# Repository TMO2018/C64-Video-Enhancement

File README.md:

# C64 Video Enhancement

The original project can be found here:
https://github.com/c0pperdragon

I've made some changes to the VIC II-Adapter pcb and the rfreplacement pcb.

# VIC II-Adapter (A-VideoBoard c64board)
Rev 3.1 is based on c0pperdragons Rev 3
- Fits better with a 407-board
- Layout for hand soldering (SMD 0805)

# rfreplacment
Rev 6.1 is based on c0pperdragons Rev 6
- Layout for hand soldering (SMD 0805)
- Video connector ist placed in the middle of the hole in the C64-housing

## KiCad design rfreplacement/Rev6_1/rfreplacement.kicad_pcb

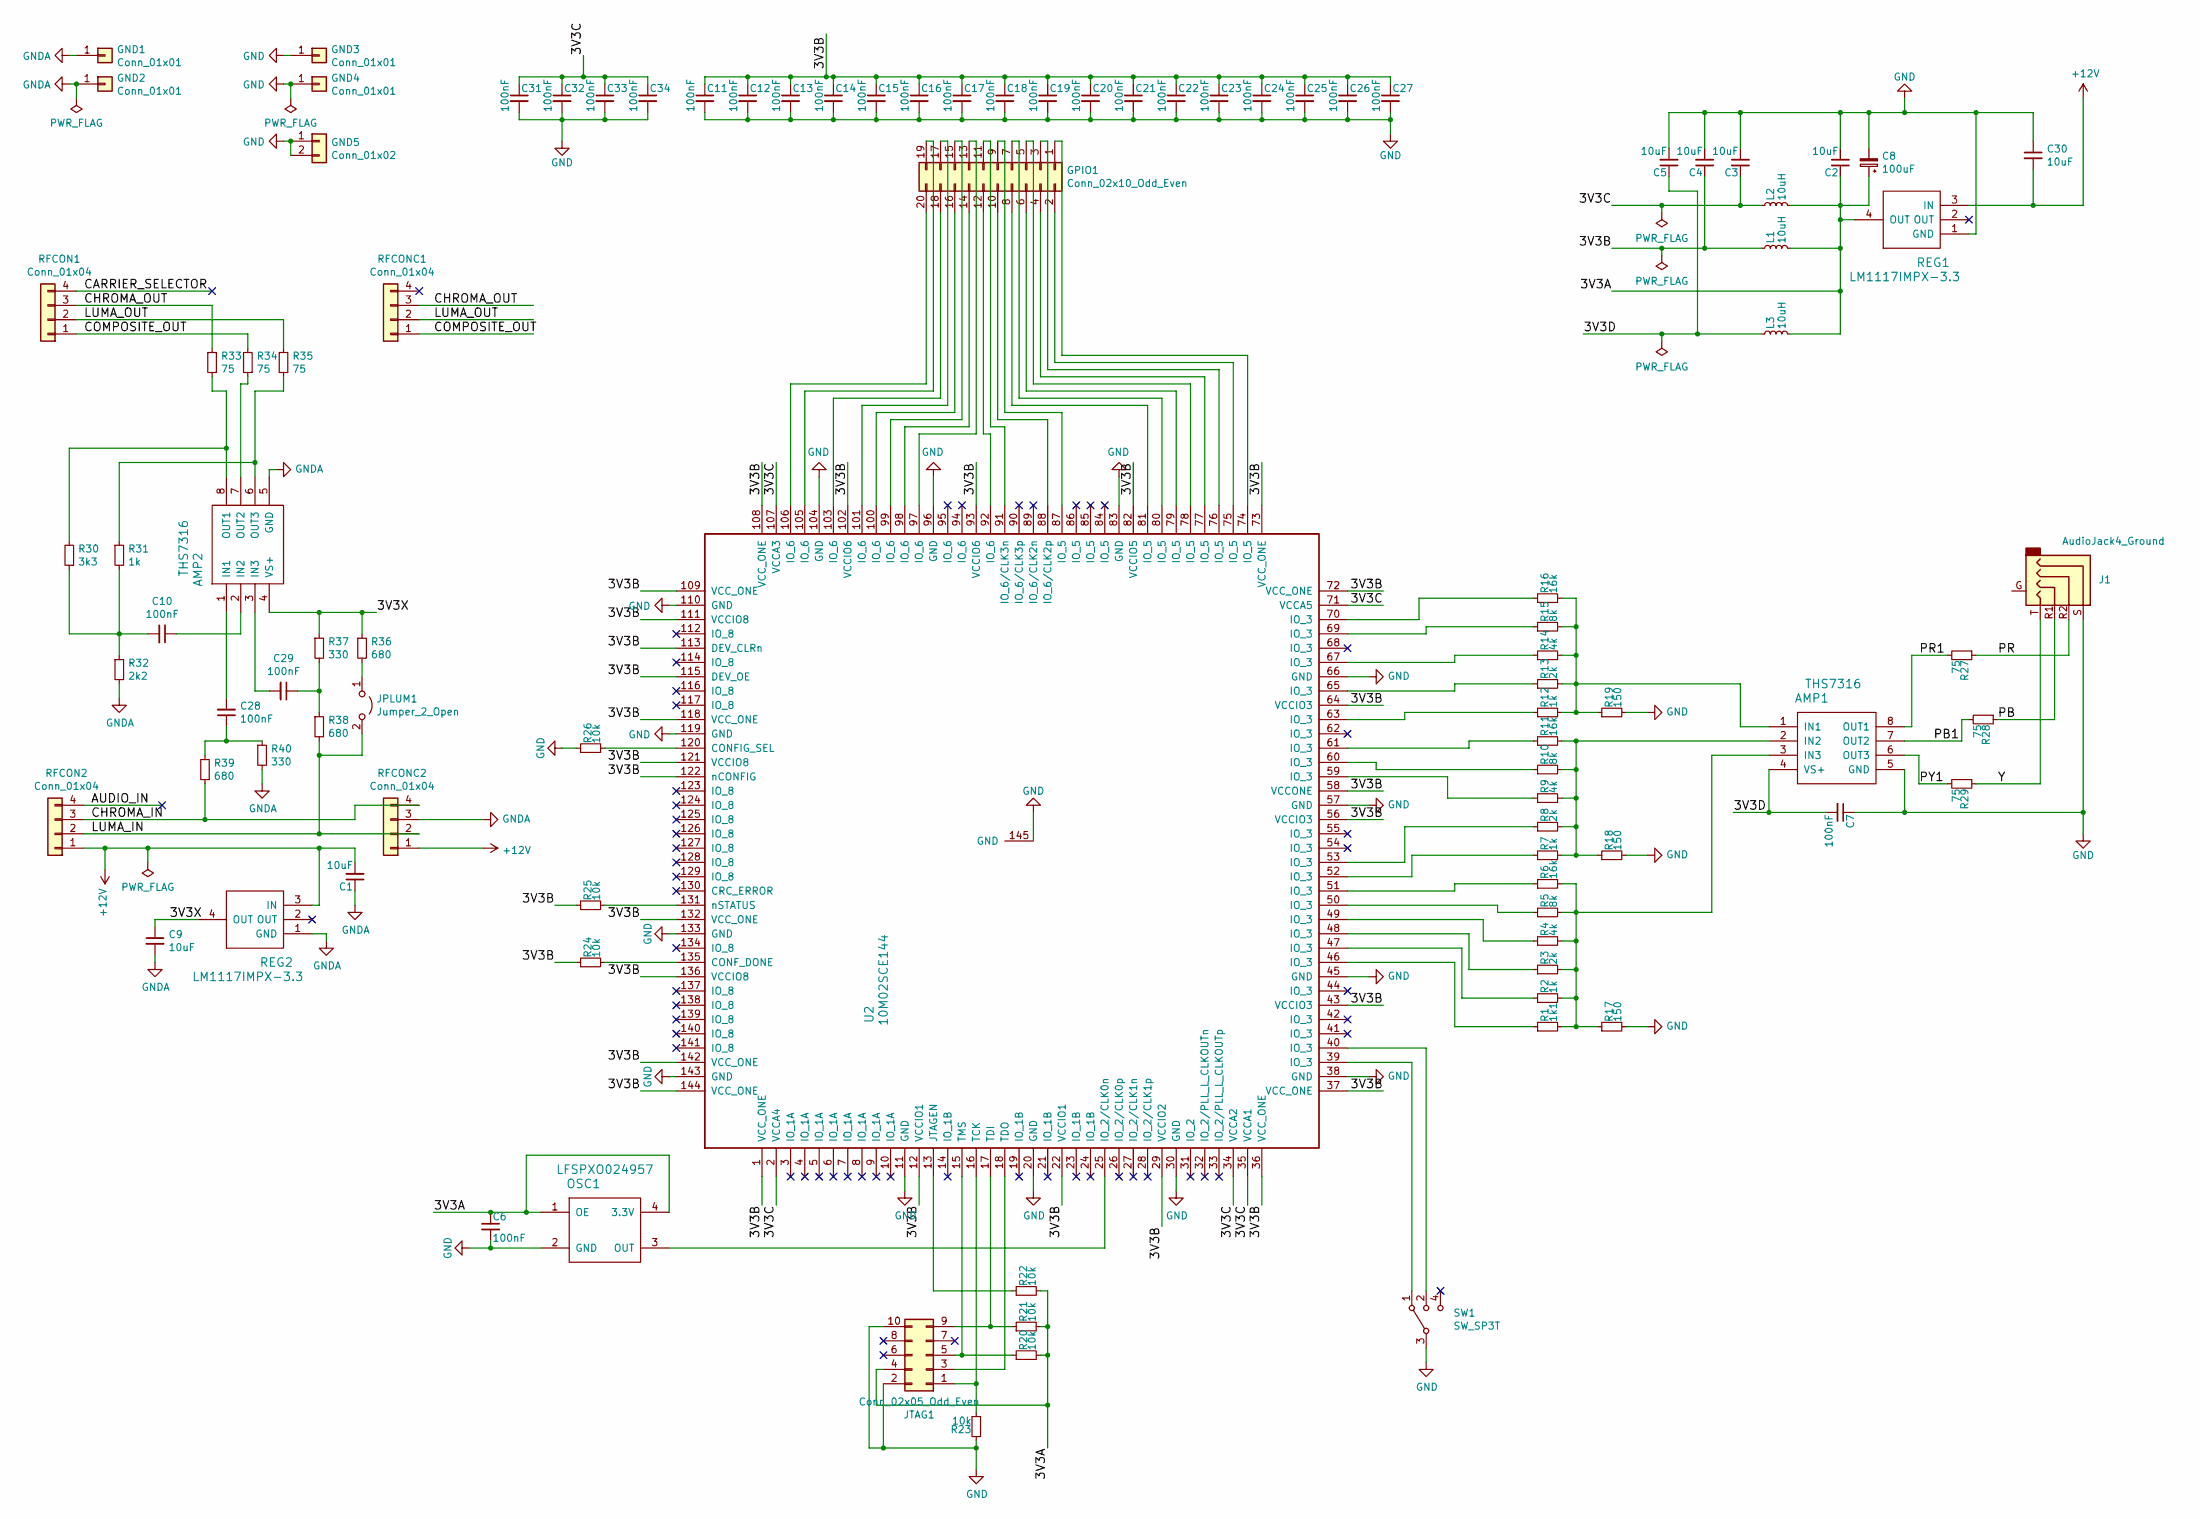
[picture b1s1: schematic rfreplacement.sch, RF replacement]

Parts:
AMP1, AMP2: THS7316; SSOP-8_3.9x5.05mm_P1.27mm
C1, C2, C3, C4, C5, C9, C30: 10uF; C_0805_HandSoldering
C6, C7, C10, C11, C12, C13, C14, C15, C16, C17, C18, C19, C20, C21, C22, C23, C24, C25, C26, C27, C28, C29, C31, C32, C33, C34: 100nF; C_0805_HandSoldering
C8: 100uF; CP_Radial_D8.0mm_P3.50mm
GND1, GND2, GND3, GND4: Conn_01x01; Pin_Header_Straight_1x01_Pitch2.54mm
GND5: Conn_01x02; Pin_Header_Straight_1x02_Pitch2.54mm
GPIO1: Conn_02x10_Odd_Even; Pin_Header_Straight_2x10_Pitch2.54mm
J1: AudioJack4_Ground; Conrad 4pin audio jack
JPLUM1: Jumper_2_Open; SolderJumper-2_P1.3mm_Open_RoundedPad1.0x1.5mm
JTAG1: Conn_02x05_Odd_Even; Pin_Header_Straight_2x05_Pitch2.54mm
L1, L2, L3: 10uH; L_0805_HandSoldering
OSC1: LFSPXO024957; Oscillator_SMD_EuroQuartz_XO53-4pin_5.0x3.2mm_HandSoldering
R1: 1k1; R_0805_HandSoldering
R2, R7, R12, R31: 1k; R_0805_HandSoldering
R3, R8, R13: 2k; R_0805_HandSoldering
R4, R9, R14: 4k; R_0805_HandSoldering
R5, R10, R15: 8k; R_0805_HandSoldering
R6, R11, R16: 16k; R_0805_HandSoldering
R17, R18, R19: 150; R_0805_HandSoldering
R20, R21, R22, R23, R24, R25, R26: 10k; R_0805_HandSoldering
R27, R28, R29, R33, R34, R35: 75; R_0805_HandSoldering
R30: 3k3; R_0805_HandSoldering
R32: 2k2; R_0805_HandSoldering
R36, R38, R39: 680; R_0805_HandSoldering
R37, R40: 330; R_0805_HandSoldering
REG1, REG2: LM1117IMPX-3.3; SOT-223
RFCON1, RFCON2: Conn_01x04; Pin_Header_Straight_1x04_Pitch2.54mm
RFCONC1, RFCONC2: Conn_01x04; Pin_Header_Straight_1x04_Pitch2.54mm
SW1: SW_SP3T; slider
U2: 10M02SCE144; EQFP-144-1EP_20x20mm_P0.5mm_EP8.93x8.7mm_ThermalVias

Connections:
+12V: C1.2, C30.2, REG1.3 (IN), REG2.3 (IN), RFCON2.1, RFCONC2.1
/3V3A: C2.1, C6.1, C8.1, JTAG1.4, L1.2, L2.2, L3.2, OSC1.1 (OE), OSC1.4 (3.3V), R20.2, R21.2, R22.2, REG1.4 (OUT)
/3V3B: C4.1, C11.1, C12.1, C13.1, C14.1, C15.1, C16.1, C17.1, C18.1, C19.1, C20.1, C21.1, C22.1, C23.1, C24.1, C25.1, C26.1, C27.1, L1.1, R24.1, R25.1, U2.1 (VCC_ONE), U2.12 (VCCIO1), U2.22 (VCCIO1), U2.29 (VCCIO2), U2.36 (VCC_ONE), U2.37 (VCC_ONE), U2.43 (VCCIO3), U2.56 (VCCIO3), U2.58 (VCCONE), U2.64 (VCCIO3), U2.72 (VCC_ONE), U2.73 (VCC_ONE), U2.82 (VCCIO5), U2.93 (VCCIO6), U2.102 (VCCIO6), U2.108 (VCC_ONE), U2.109 (VCC_ONE), U2.111 (VCCIO8), U2.113 (DEV_CLRn), U2.115 (DEV_OE), U2.118 (VCC_ONE), U2.121 (VCCIO8), U2.122 (nCONFIG), U2.132 (VCC_ONE), U2.136 (VCCIO8), U2.142 (VCC_ONE), U2.144 (VCC_ONE)
/3V3C: C3.1, C31.1, C32.1, C33.1, C34.1, L2.1, U2.2 (VCCA4), U2.34 (VCCA2), U2.35 (VCCA1), U2.71 (VCCA5), U2.107 (VCCA3)
/3V3D: AMP1.4 (VS+), C5.1, C7.2, L3.1
/3V3X: AMP2.4 (VS+), C9.1, R36.1, R37.1, REG2.4 (OUT)
/CHROMA_IN: R39.1, RFCON2.3, RFCONC2.4
/CHROMA_OUT: R33.1, RFCON1.3, RFCONC1.3
/COMPOSITE_OUT: R34.2, RFCON1.1, RFCONC1.1
/LUMA_IN: JPLUM1.2 (B), R38.2, RFCON2.2, RFCONC2.2
/LUMA_OUT: R35.1, RFCON1.2, RFCONC1.2
/PB: J1.R1, R28.1
/PB1: AMP1.7 (OUT2), R28.2
/PR: J1.R2, R27.1
/PR1: AMP1.8 (OUT1), R27.2
/PY1: AMP1.6 (OUT3), R29.2
/Y: J1.T, R29.1
GND: AMP1.5 (GND), C2.2, C3.2, C4.2, C5.2, C6.2, C7.1, C8.2, C11.2, C12.2, C13.2, C14.2, C15.2, C16.2, C17.2, C18.2, C19.2, C20.2, C21.2, C22.2, C23.2, C24.2, C25.2, C26.2, C27.2, C30.1, C31.2, C32.2, C33.2, C34.2, GND3.1, GND4.1, GND5.1, GND5.2, J1.S, JTAG1.2, JTAG1.10, OSC1.2 (GND), R17.2, R18.2, R19.2, R23.1, R26.1, REG1.1 (GND), SW1.3, U2.11 (GND), U2.20 (GND), U2.30 (GND), U2.38 (GND), U2.45 (GND), U2.57 (GND), U2.66 (GND), U2.83 (GND), U2.96 (GND), U2.104 (GND), U2.110 (GND), U2.119 (GND), U2.133 (GND), U2.143 (GND), U2.145 (GND)
GNDA: AMP2.5 (GND), C1.1, C9.2, GND1.1, GND2.1, R32.2, R40.2, REG2.1 (GND), RFCONC2.3
unnamed: AMP1.1 (IN1), R12.2, R13.2, R14.2, R15.2, R16.2, R19.1
unnamed: AMP1.2 (IN2), R7.2, R8.2, R9.2, R10.2, R11.2, R18.1
unnamed: AMP1.3 (IN3), R1.2, R2.2, R3.2, R4.2, R5.2, R6.2, R17.1
unnamed: AMP2.1 (IN1), C28.2
unnamed: AMP2.2 (IN2), C10.1
unnamed: AMP2.3 (IN3), C29.2
unnamed: AMP2.6 (OUT3), R31.1, R35.2
unnamed: AMP2.7 (OUT2), R34.1
unnamed: AMP2.8 (OUT1), R30.2, R33.2
unnamed: C10.2, R30.1, R31.2, R32.1
unnamed: C28.1, R39.2, R40.1
unnamed: C29.1, R37.2, R38.1
unnamed: GPIO1.1, U2.74 (IO_5)
unnamed: GPIO1.2, U2.75 (IO_5)
unnamed: GPIO1.3, U2.76 (IO_5)
unnamed: GPIO1.4, U2.77 (IO_5)
unnamed: GPIO1.5, U2.78 (IO_5)
unnamed: GPIO1.6, U2.79 (IO_5)
unnamed: GPIO1.7, U2.80 (IO_5)
unnamed: GPIO1.8, U2.81 (IO_5)
unnamed: GPIO1.9, U2.87 (IO_5)
unnamed: GPIO1.10, U2.88 (IO_6/CLK2p)
unnamed: GPIO1.11, U2.91 (IO_6/CLK3n)
unnamed: GPIO1.12, U2.92 (IO_6)
unnamed: GPIO1.13, U2.97 (IO_6)
unnamed: GPIO1.14, U2.98 (IO_6)
unnamed: GPIO1.15, U2.99 (IO_6)
unnamed: GPIO1.16, U2.100 (IO_6)
unnamed: GPIO1.17, U2.101 (IO_6)
unnamed: GPIO1.18, U2.103 (IO_6)
unnamed: GPIO1.19, U2.105 (IO_6)
unnamed: GPIO1.20, U2.106 (IO_6)
unnamed: JPLUM1.1 (A), R36.2
unnamed: JTAG1.1, R23.2, U2.16 (TCK)
unnamed: JTAG1.3, U2.18 (TDO)
unnamed: JTAG1.5, R20.1, U2.15 (TMS)
unnamed: JTAG1.9, R21.1, U2.17 (TDI)
unnamed: OSC1.3 (OUT), U2.25 (IO_2/CLK0n)
unnamed: R1.1, U2.46 (IO_3)
unnamed: R2.1, U2.47 (IO_3)
unnamed: R3.1, U2.48 (IO_3)
unnamed: R4.1, U2.49 (IO_3)
unnamed: R5.1, U2.50 (IO_3)
unnamed: R6.1, U2.51 (IO_3)
unnamed: R7.1, U2.52 (IO_3)
unnamed: R8.1, U2.53 (IO_3)
unnamed: R9.1, U2.59 (IO_3)
unnamed: R10.1, U2.60 (IO_3)
unnamed: R11.1, U2.61 (IO_3)
unnamed: R12.1, U2.63 (IO_3)
unnamed: R13.1, U2.65 (IO_3)
unnamed: R14.1, U2.67 (IO_3)
unnamed: R15.1, U2.69 (IO_3)
unnamed: R16.1, U2.70 (IO_3)
unnamed: R22.1, U2.13 (JTAGEN)
unnamed: R24.2, U2.135 (CONF_DONE)
unnamed: R25.2, U2.131 (nSTATUS)
unnamed: R26.2, U2.120 (CONFIG_SEL)
unnamed: SW1.1, U2.39 (IO_3)
unnamed: SW1.2, U2.40 (IO_3)

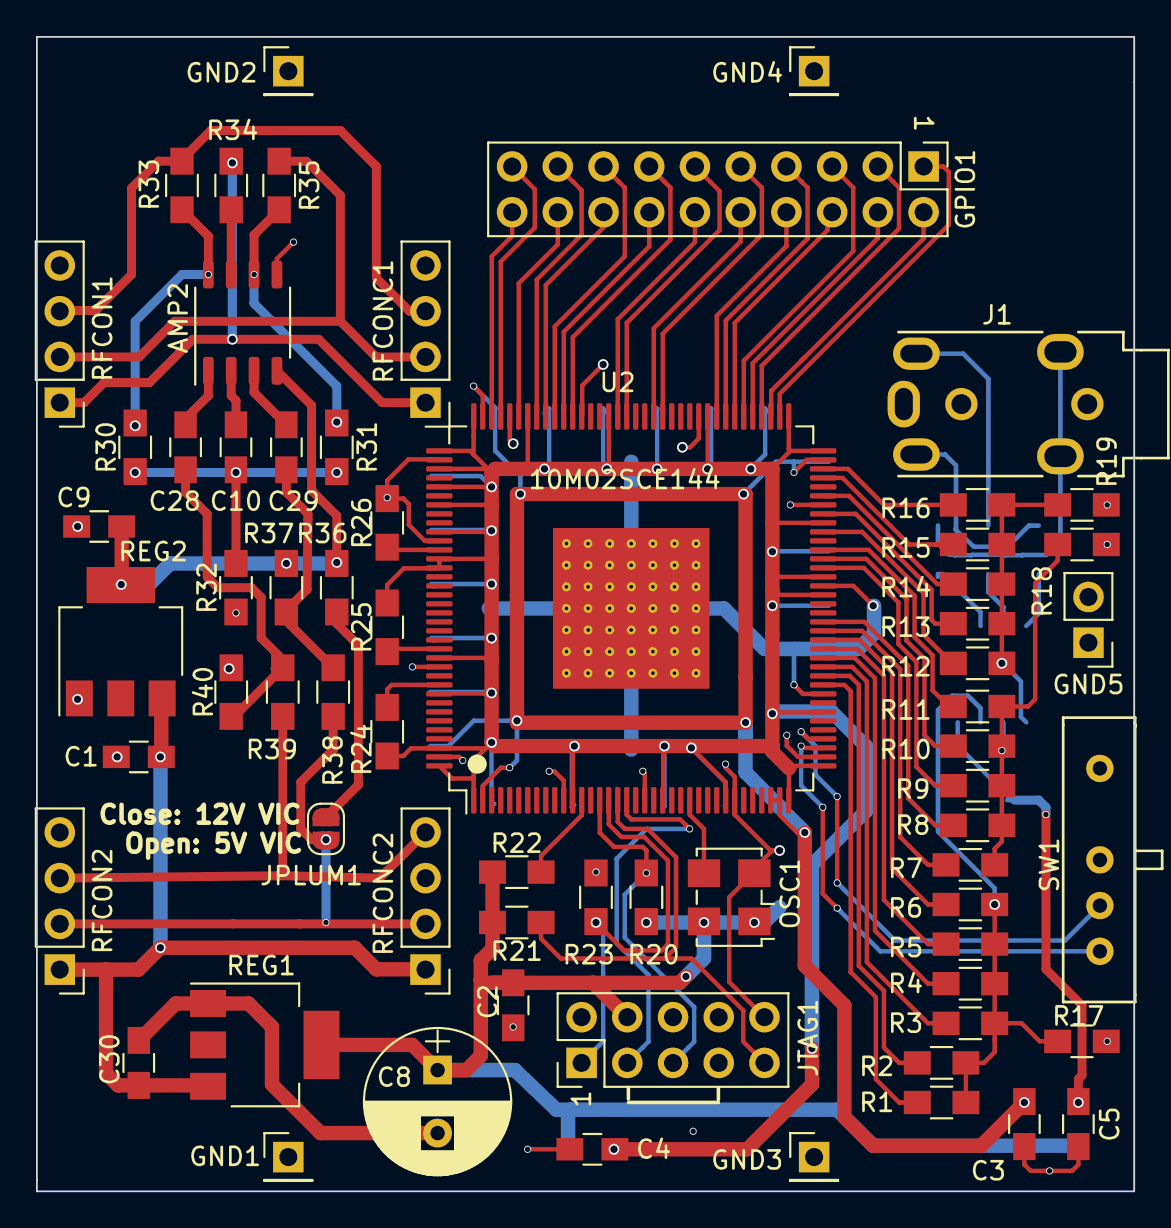
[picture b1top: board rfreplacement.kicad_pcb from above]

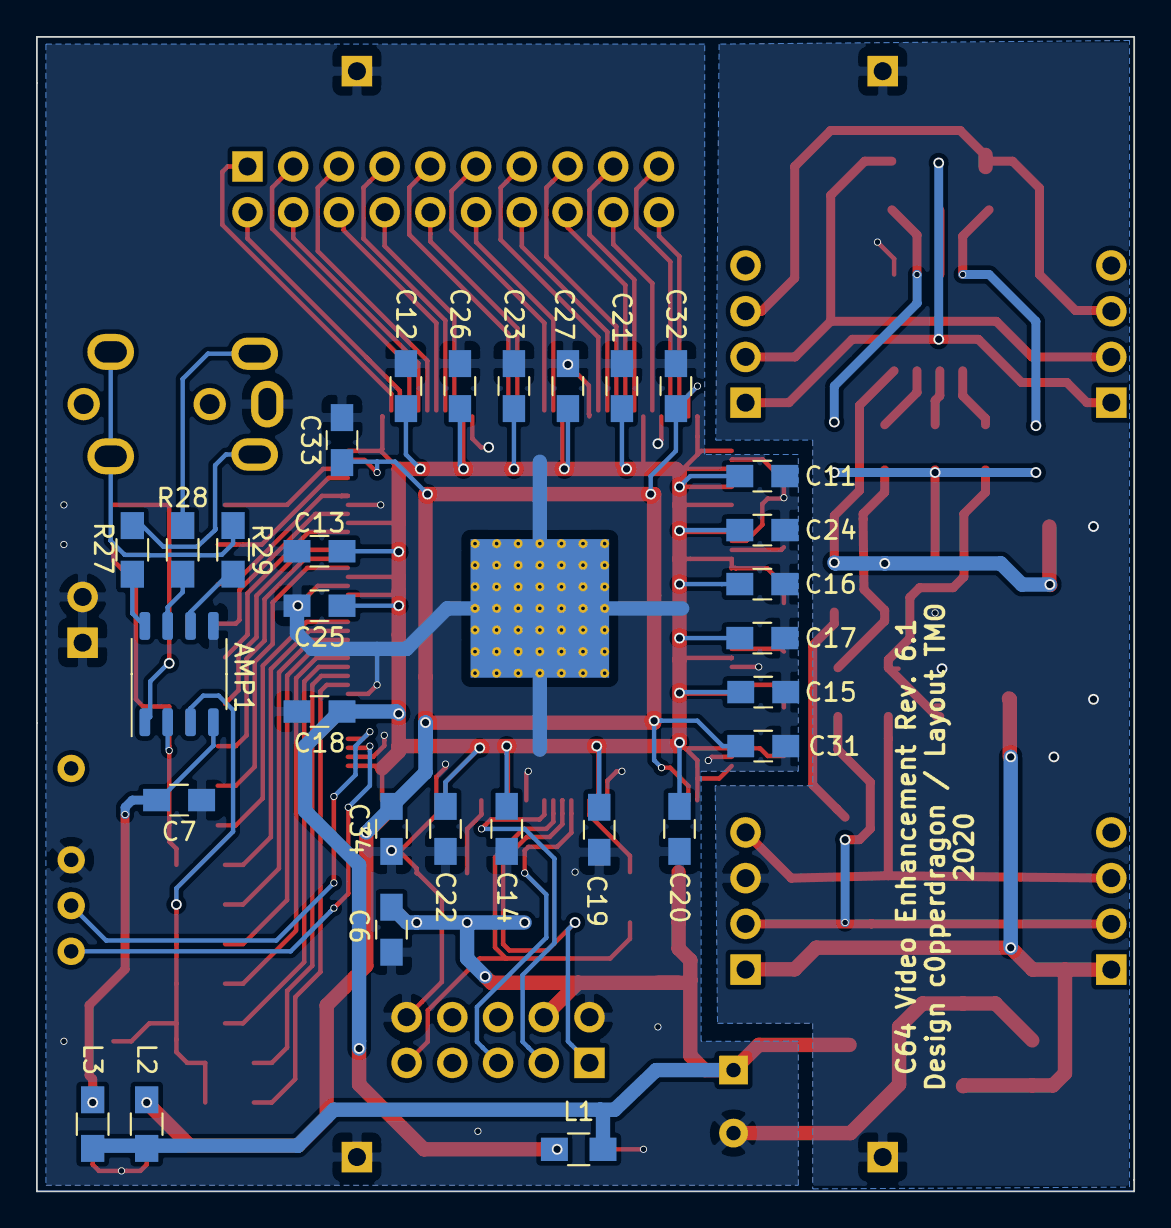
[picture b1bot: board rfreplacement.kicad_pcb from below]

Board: 2 copper layers, 61.0 x 64.1 mm, 97 parts (30 on the bottom side), 79 nets.

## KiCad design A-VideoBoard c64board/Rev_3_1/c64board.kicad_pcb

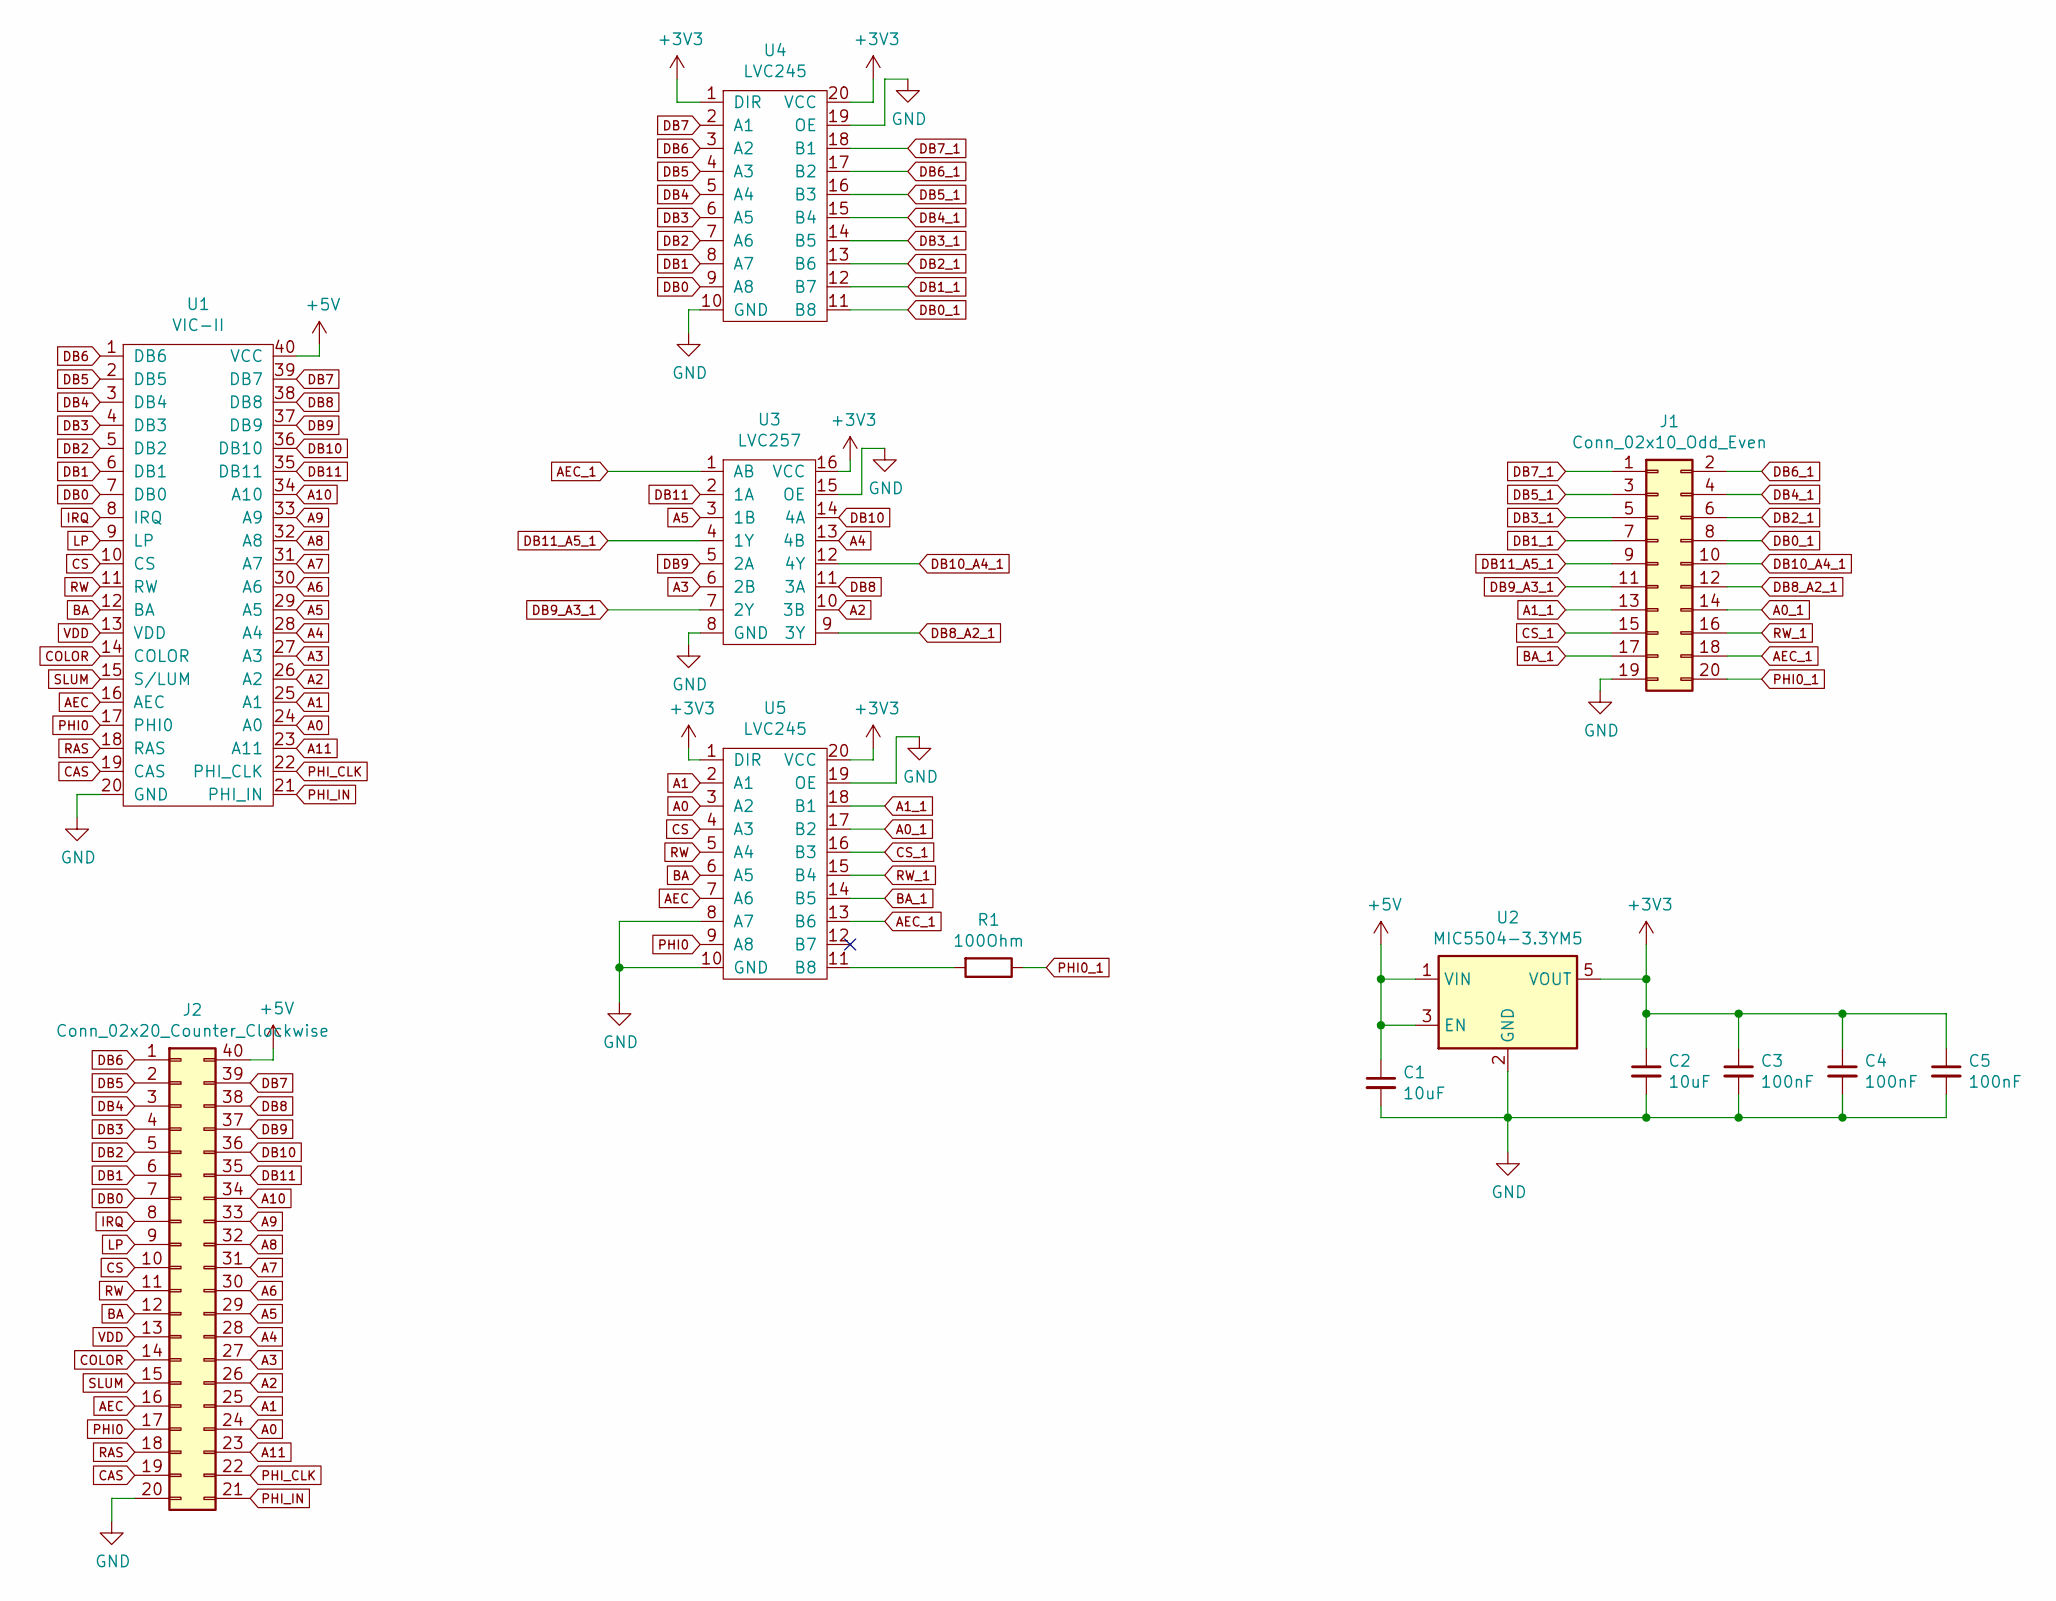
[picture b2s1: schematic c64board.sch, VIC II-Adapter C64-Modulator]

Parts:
C1, C2: 10uF; C_0805_HandSoldering
C3, C4, C5: 100nF; C_0805_HandSoldering
J1: Conn_02x10_Odd_Even; Pin_Header_Straight_2x10_Pitch2.54mm
J2: Conn_02x20_Counter_Clockwise; DIP-40_W15.24mm_LongPads
R1: 100Ohm; R_0805_HandSoldering
U1: VIC-II; DIP-40_W15.24mm_Socket_LongPads
U2: MIC5504-3.3YM5; SOT-23-5_HandSoldering
U3: LVC257; TSSOP-16_4.4x5mm_Pitch0.65mm
U4, U5: LVC245; TSSOP-20_4.4x6.5mm_Pitch0.65mm

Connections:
+3V3: C2.1, C3.1, C4.1, C5.1, U2.5 (VOUT), U3.16 (VCC), U4.1 (DIR), U4.20 (VCC), U5.1 (DIR), U5.20 (VCC)
+5V: C1.1, J2.40, U1.40 (VCC), U2.1 (VIN), U2.3 (EN)
A0: J2.24, U1.24 (A0), U5.3 (A2)
A0_1: J1.14, U5.17 (B2)
A1: J2.25, U1.25 (A1), U5.2 (A1)
A1_1: J1.13, U5.18 (B1)
A2: J2.26, U1.26 (A2), U3.10 (3B)
A3: J2.27, U1.27 (A3), U3.6 (2B)
A4: J2.28, U1.28 (A4), U3.13 (4B)
A5: J2.29, U1.29 (A5), U3.3 (1B)
A6: J2.30, U1.30 (A6)
A7: J2.31, U1.31 (A7)
A8: J2.32, U1.32 (A8)
A9: J2.33, U1.33 (A9)
A10: J2.34, U1.34 (A10)
A11: J2.23, U1.23 (A11)
AEC: J2.16, U1.16 (AEC), U5.7 (A6)
AEC_1: J1.18, U3.1 (AB), U5.13 (B6)
BA: J2.12, U1.12 (BA), U5.6 (A5)
BA_1: J1.17, U5.14 (B5)
CAS: J2.19, U1.19 (CAS)
COLOR: J2.14, U1.14 (COLOR)
CS: J2.10, U1.10 (CS), U5.4 (A3)
CS_1: J1.15, U5.16 (B3)
DB0: J2.7, U1.7 (DB0), U4.9 (A8)
DB0_1: J1.8, U4.11 (B8)
DB1: J2.6, U1.6 (DB1), U4.8 (A7)
DB1_1: J1.7, U4.12 (B7)
DB2: J2.5, U1.5 (DB2), U4.7 (A6)
DB2_1: J1.6, U4.13 (B6)
DB3: J2.4, U1.4 (DB3), U4.6 (A5)
DB3_1: J1.5, U4.14 (B5)
DB4: J2.3, U1.3 (DB4), U4.5 (A4)
DB4_1: J1.4, U4.15 (B4)
DB5: J2.2, U1.2 (DB5), U4.4 (A3)
DB5_1: J1.3, U4.16 (B3)
DB6: J2.1, U1.1 (DB6), U4.3 (A2)
DB6_1: J1.2, U4.17 (B2)
DB7: J2.39, U1.39 (DB7), U4.2 (A1)
DB7_1: J1.1, U4.18 (B1)
DB8: J2.38, U1.38 (DB8), U3.11 (3A)
DB8_A2_1: J1.12, U3.9 (3Y)
DB9: J2.37, U1.37 (DB9), U3.5 (2A)
DB9_A3_1: J1.11, U3.7 (2Y)
DB10: J2.36, U1.36 (DB10), U3.14 (4A)
DB10_A4_1: J1.10, U3.12 (4Y)
DB11: J2.35, U1.35 (DB11), U3.2 (1A)
DB11_A5_1: J1.9, U3.4 (1Y)
GND: C1.2, C2.2, C3.2, C4.2, C5.2, J1.19, J2.20, U1.20 (GND), U2.2 (GND), U3.8 (GND), U3.15 (OE), U4.10 (GND), U4.19 (OE), U5.8 (A7), U5.10 (GND), U5.19 (OE)
IRQ: J2.8, U1.8 (IRQ)
LP: J2.9, U1.9 (LP)
unnamed: R1.2, U5.11 (B8)
PHI0: J2.17, U1.17 (PHI0), U5.9 (A8)
PHI0_1: J1.20, R1.1
PHI_CLK: J2.22, U1.22 (PHI_CLK)
PHI_IN: J2.21, U1.21 (PHI_IN)
RAS: J2.18, U1.18 (RAS)
RW: J2.11, U1.11 (RW), U5.5 (A4)
RW_1: J1.16, U5.15 (B4)
SLUM: J2.15, U1.15 (S/LUM)
VDD: J2.13, U1.13 (VDD)

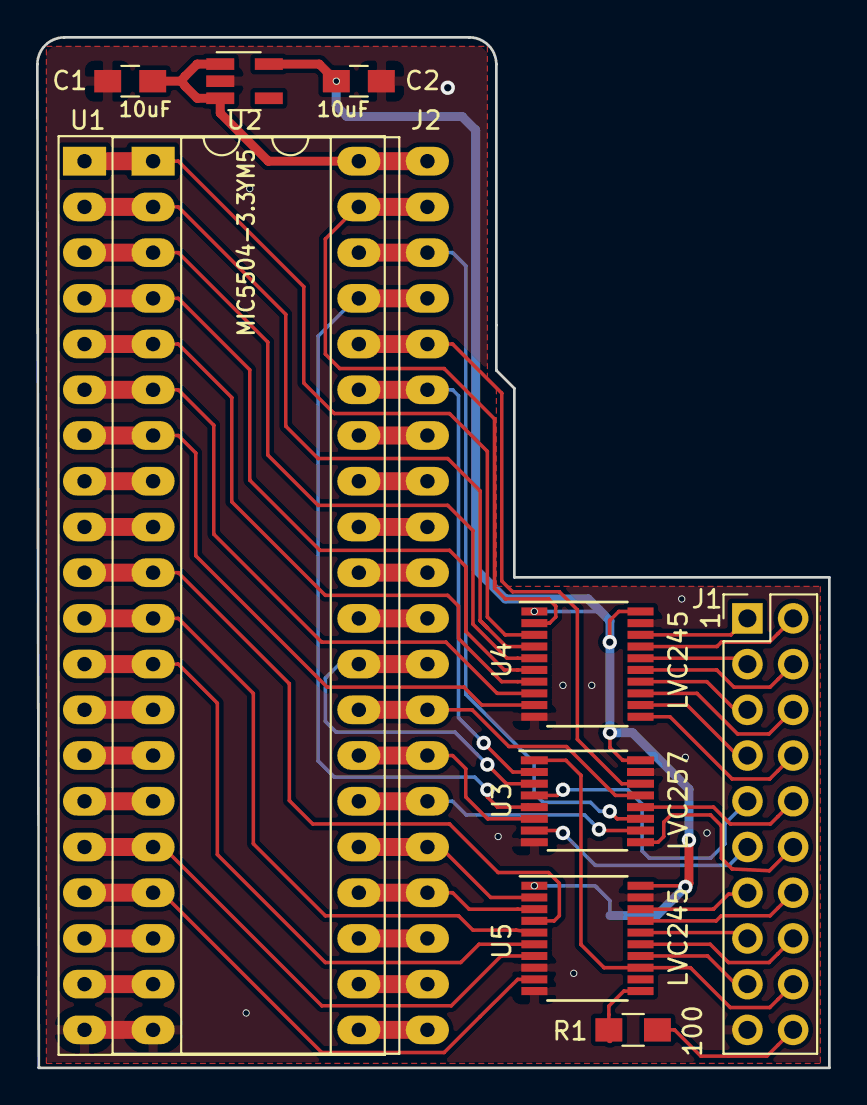
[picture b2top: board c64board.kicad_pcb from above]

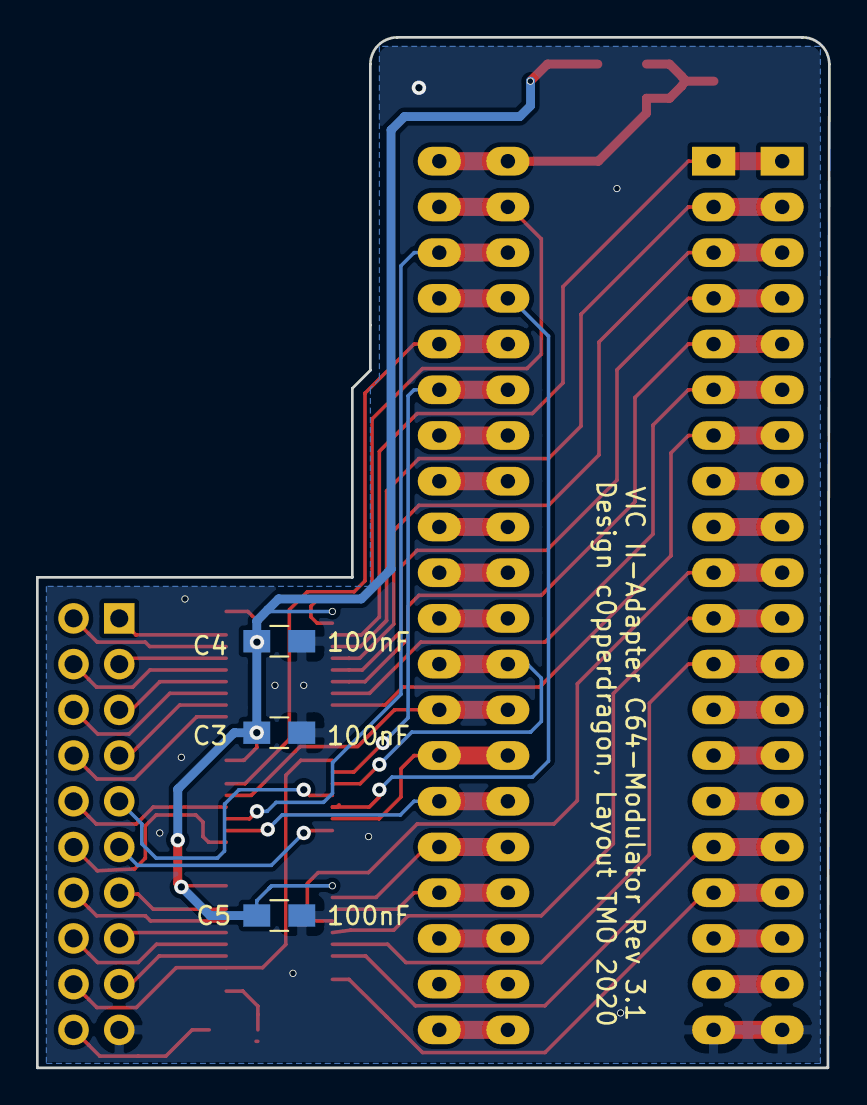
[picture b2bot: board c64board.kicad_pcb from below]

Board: 2 copper layers, 44.0 x 57.2 mm, 13 parts (3 on the bottom side), 61 nets.
